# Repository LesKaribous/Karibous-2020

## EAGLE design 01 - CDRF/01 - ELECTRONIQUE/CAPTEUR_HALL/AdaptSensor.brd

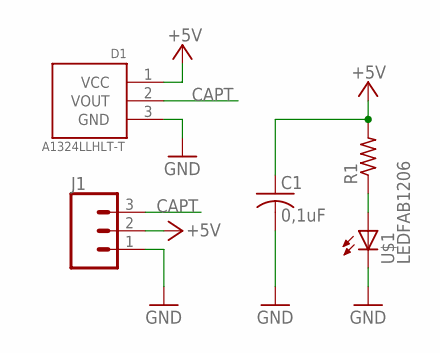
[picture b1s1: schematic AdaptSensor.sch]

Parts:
C1: 0,1uF; C1206FAB
D1: A1324LLHLT-T; SOT190P290X100-3N
J1: CONN_03POLAR; MOLEX-1X3
R1: RES-US1206FAB; R1206FAB
U$1: LEDFAB1206; LED1206FAB

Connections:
+5V: C1.1, D1.1 (VCC), J1.2, R1.2
CAPT: D1.2 (VOUT), J1.3
GND: C1.2, D1.3 (GND), J1.1, U$1.2 (C)
unnamed: R1.1, U$1.1 (A)

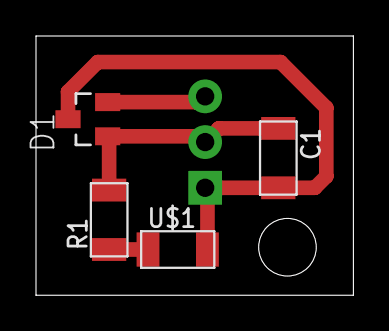
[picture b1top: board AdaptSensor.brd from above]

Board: 2 copper layers, 17.6 x 14.4 mm, 5 parts (1 on the bottom side), 4 nets.

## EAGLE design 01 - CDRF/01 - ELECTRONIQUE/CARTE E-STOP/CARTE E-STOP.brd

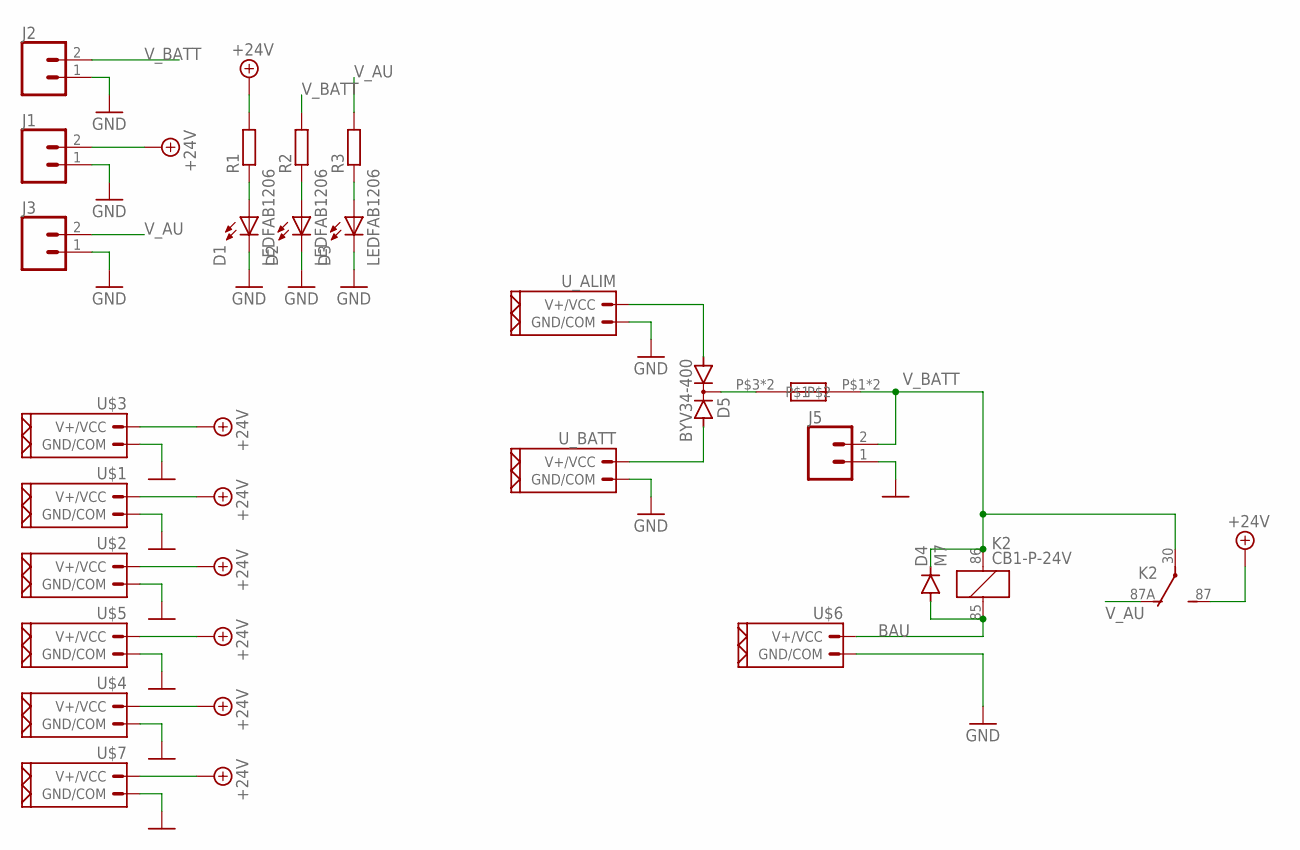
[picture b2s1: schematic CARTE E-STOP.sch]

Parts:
D1, D2, D3: LEDFAB1206; LED1206FAB
D4: M7; SMA-DO214AC
D5: BYV34-400; TO220ABS
J1, J2, J3, J5: CONN_02POLAR; MOLEX-1X2
K2: CB1-P-24V; CB1
R1, R2, R3: R-EU_M1206; M1206
U$1, U$2, U$3, U$4, U$5, U$7: CONN_02_PUIXT30; XT30_FEMALE
U$6: CONN_02_PUI; NSK396-2C
U$8: AUTOMOTIVE_FUSE3557-2; 3557-2
U_ALIM: CONN_02_PUIXT60; XT60
U_BATT: CONN_02_PUIXT60; XT60

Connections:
+24V: J1.2, K2.87 (S), R1.2, U$1.P$1 (V+/VCC), U$2.P$1 (V+/VCC), U$3.P$1 (V+/VCC), U$4.P$1 (V+/VCC), U$5.P$1 (V+/VCC), U$7.P$1 (V+/VCC)
BAU: D4.A, K2.85 (2), U$6.P$2 (V+/VCC)
GND: D1.2 (C), D2.2 (C), D3.2 (C), J1.1, J2.1, J3.1, J5.1, U$1.P$2 (GND/COM), U$2.P$2 (GND/COM), U$3.P$2 (GND/COM), U$4.P$2 (GND/COM), U$5.P$2 (GND/COM), U$6.P$1 (GND/COM), U$7.P$2 (GND/COM), U_ALIM.P$2 (GND/COM), U_BATT.P$2 (GND/COM)
unnamed: D1.1 (A), R1.1
unnamed: D2.1 (A), R2.1
unnamed: D3.1 (A), R3.1
unnamed: D5.A1, U_ALIM.P$1 (V+/VCC)
unnamed: D5.C, U$8.P$3, U$8.P$4
unnamed: D5.A2, U_BATT.P$1 (V+/VCC)
V_AU: J3.2, K2.87A (O), R3.2
V_BATT: D4.K (C), J2.2, J5.2, K2.30, K2.86 (1), R2.2, U$8.P$1, U$8.P$2

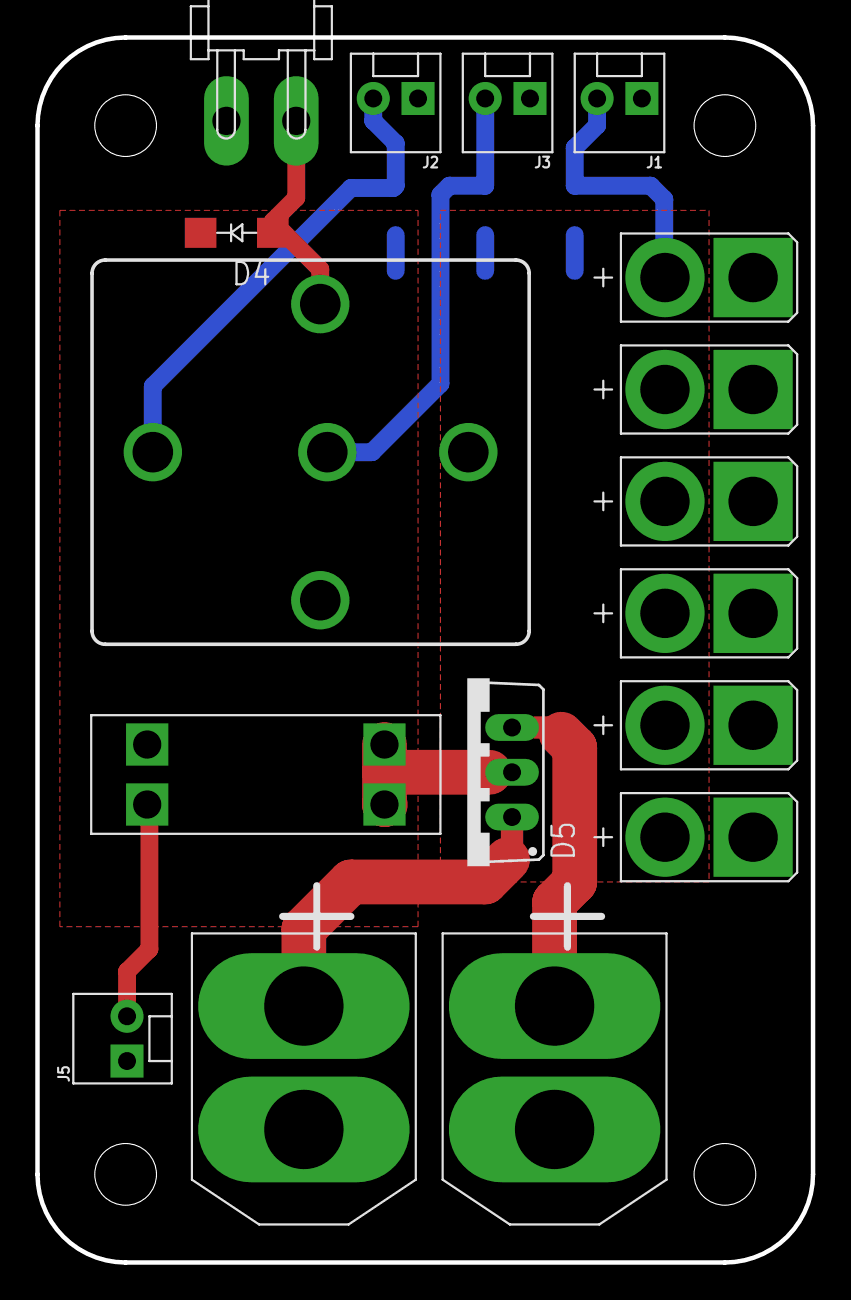
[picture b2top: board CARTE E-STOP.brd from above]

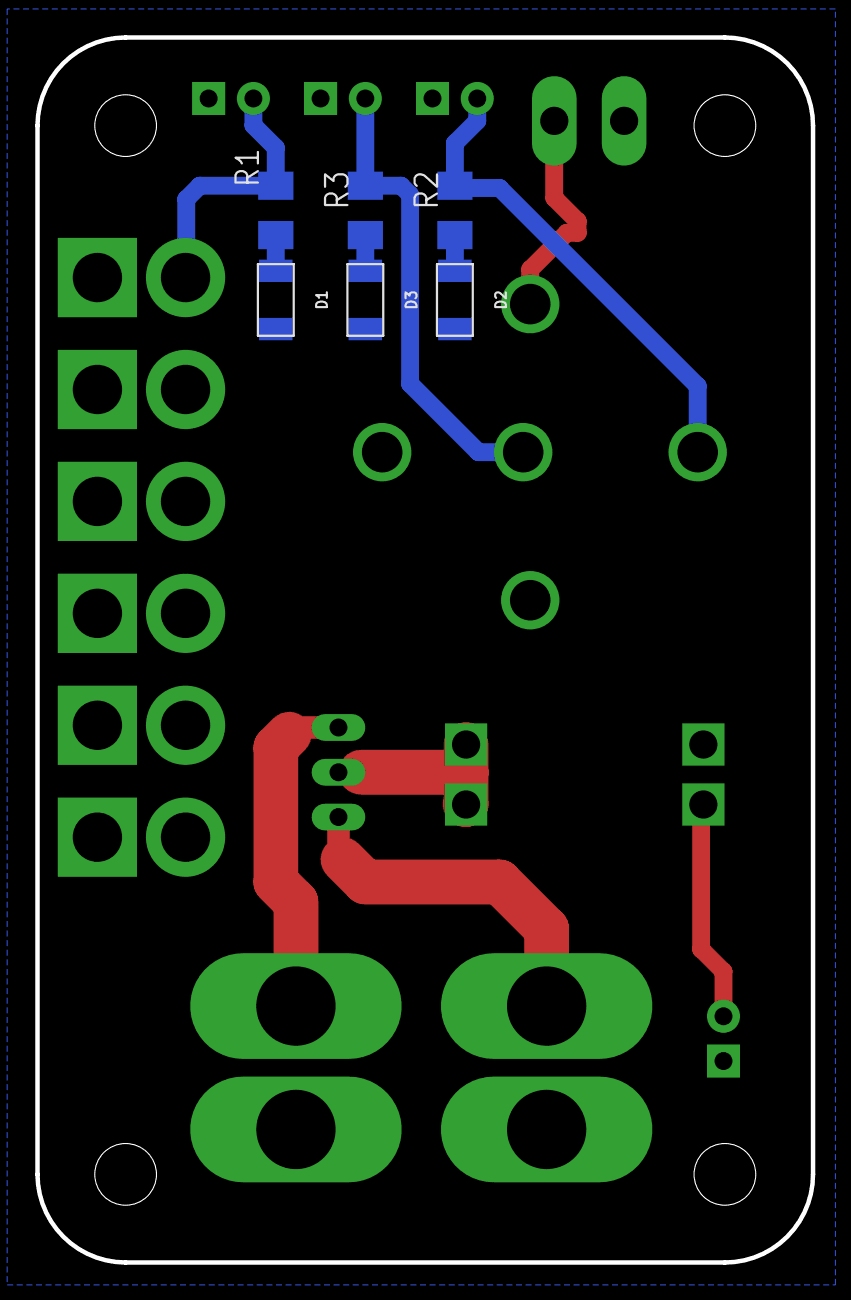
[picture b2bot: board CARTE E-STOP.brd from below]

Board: 2 copper layers, 44.0 x 69.5 mm, 23 parts (6 on the bottom side), 11 nets.

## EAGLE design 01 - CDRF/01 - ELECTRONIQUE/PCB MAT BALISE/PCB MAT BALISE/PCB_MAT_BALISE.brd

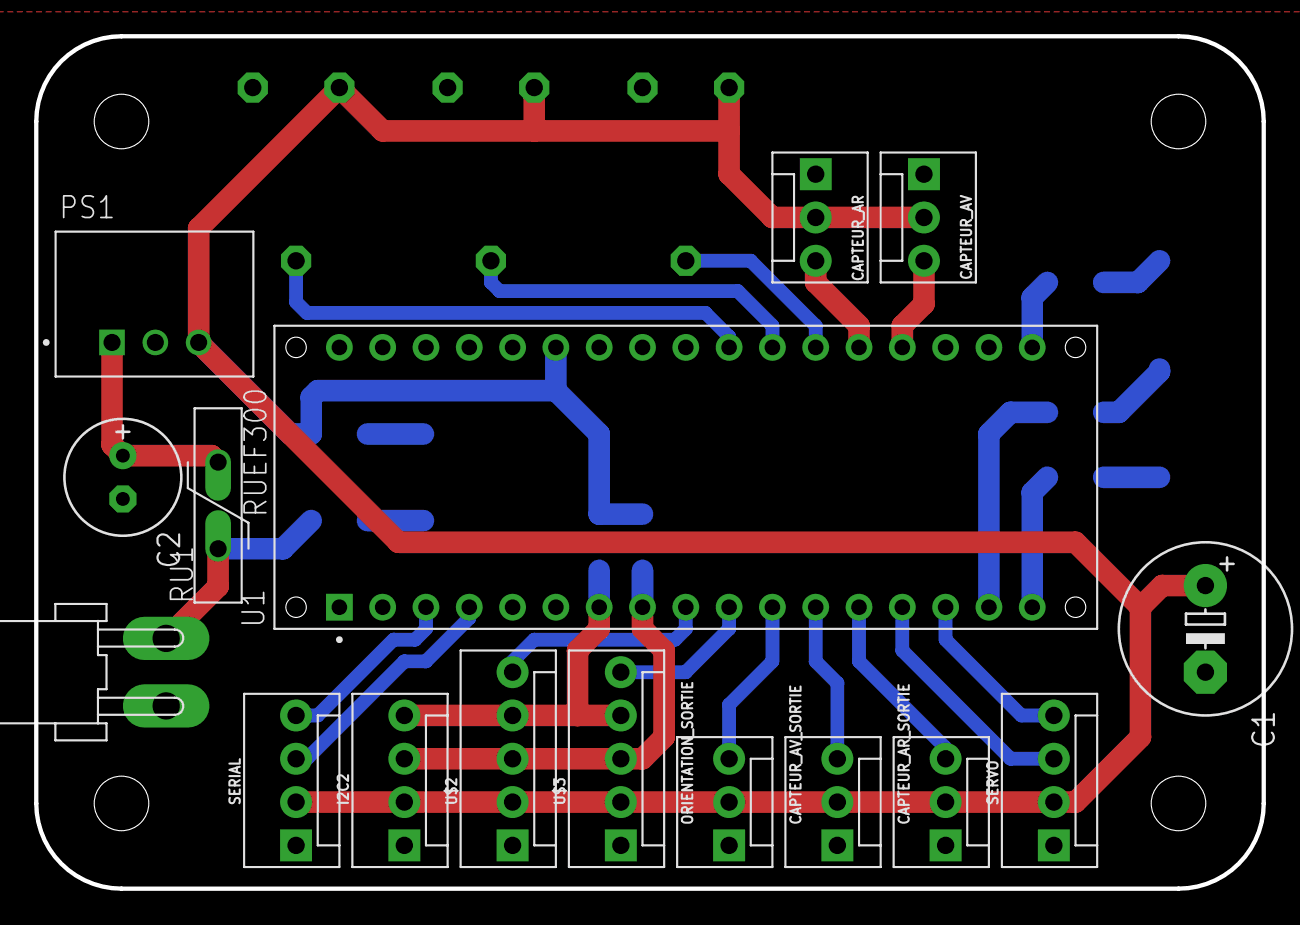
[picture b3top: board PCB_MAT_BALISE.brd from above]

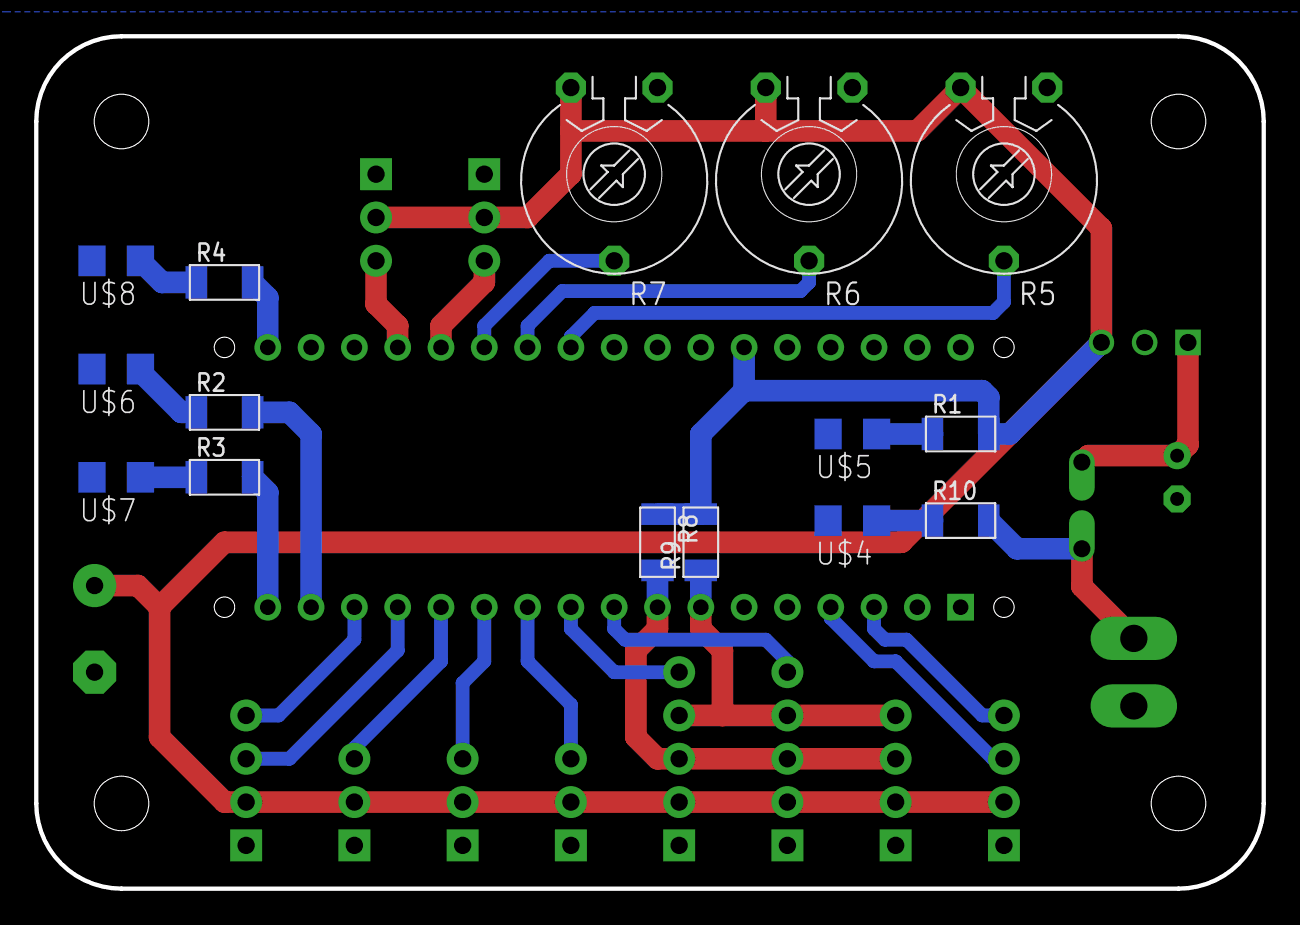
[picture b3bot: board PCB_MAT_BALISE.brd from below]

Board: 2 copper layers, 72.0 x 50.0 mm, 31 parts (15 on the bottom side), 28 nets.

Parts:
C1: 470uF; E5-10,5
C2: 10uF; E2,5-7
CAPTEUR_AR: MOLEX-1X3
CAPTEUR_AR_SORTIE: MOLEX-1X3
CAPTEUR_AV: MOLEX-1X3
CAPTEUR_AV_SORTIE: MOLEX-1X3
I2C2: MOLEX-1X4
ORIENTATION_SORTIE: MOLEX-1X3
PS1: R-78E5.0-1.0; CONV_R-78E5.0-1.0
R1, R2, R3, R4, R8, R9, R10: R1206FAB
R5, R6, R7: PT-10
RU1: RUEF300
SERIAL: MOLEX-1X4
SERVO: MOLEX-1X4
U1: A000053; ARDUINO_A000053
U$1: CONN_02_PUI; NSK396-2C
U$2, U$3: CONN_05; MOLEX-1X5
U$4, U$5, U$6, U$7, U$8: LED; LED1206

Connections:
+5V: C1.+, CAPTEUR_AR.2, CAPTEUR_AR_SORTIE.2, CAPTEUR_AV.2, CAPTEUR_AV_SORTIE.2, I2C2.2, ORIENTATION_SORTIE.2, PS1.3, R1.2, R5.2, R6.2, R7.2, R8.1, R9.2, SERIAL.2, SERVO.2, U1.29, U$2.2, U$3.2
+24V: R10.2, RU1.P$1, U$1.P$2
CAPT_AR: CAPTEUR_AR.3, U1.22
CAPT_AR_SORTIE: CAPTEUR_AR_SORTIE.3, U1.13
CAPT_AV: CAPTEUR_AV.3, U1.21
CAPT_AV_SORTIE: CAPTEUR_AV_SORTIE.3, U1.12
DETECT_AR: R3.2, U1.17
DETECT_AV: R2.2, U1.16
EMITT_1: R4.2, U1.18
GND: C1.-, C2.-, CAPTEUR_AR.1, CAPTEUR_AR_SORTIE.1, CAPTEUR_AV.1, CAPTEUR_AV_SORTIE.1, I2C2.1, ORIENTATION_SORTIE.1, PS1.2, R5.1, R6.1, R7.1, SERIAL.1, SERVO.1, U1.6, U1.31, U$1.P$1, U$2.1, U$3.1, U$4.2, U$5.2, U$6.2, U$7.2, U$8.2
unnamed: R1.1, U$5.1
unnamed: R2.1, U$6.1
unnamed: R3.1, U$7.1
unnamed: R4.1, U$8.1
unnamed: C2.+, PS1.1, RU1.P$2
unnamed: R10.1, U$4.1
ORIENTATION_SORTIE: ORIENTATION_SORTIE.3, U1.11
RX: SERIAL.3, U1.4
SCL: I2C2.3, R8.2, U1.8, U$2.3, U$3.3
SDA: I2C2.4, R9.1, U1.7, U$2.4, U$3.4
SIGNAL_1: R6.3, U1.24
SIGNAL_2: R5.3, U1.25
SIGNAL_ORIENTATION: SERVO.3, U1.14
SIGNAL_SERVO: SERVO.4, U1.15
TX: SERIAL.4, U1.3
VITESSE_SERVO: R7.3, U1.23
XSHUT_AR: U1.9, U$2.5
XSHUT_AV: U1.10, U$3.5

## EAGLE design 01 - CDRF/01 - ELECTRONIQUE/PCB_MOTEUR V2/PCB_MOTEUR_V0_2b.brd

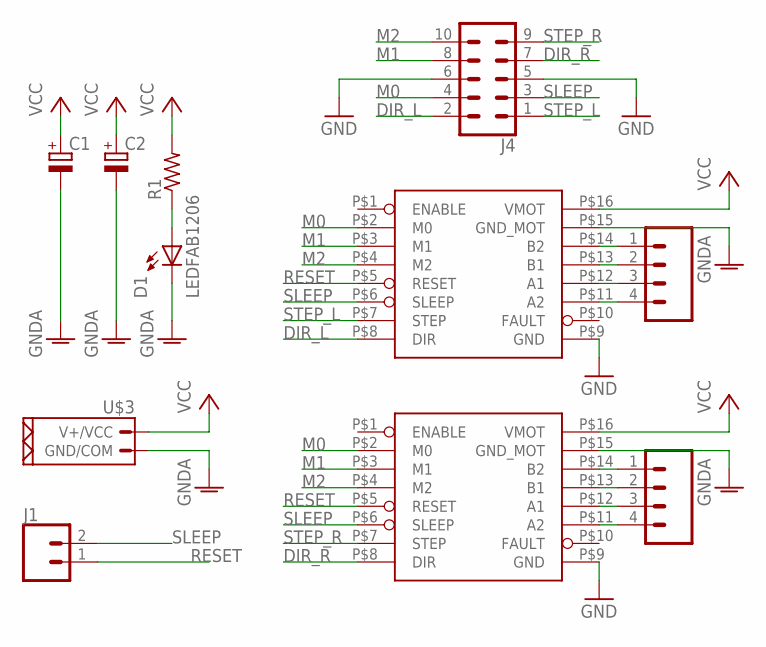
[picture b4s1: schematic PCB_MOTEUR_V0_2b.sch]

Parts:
C1, C2: CPOL-EUE3.5-8; E3,5-8
D1: LEDFAB1206; LED1206FAB
J1: CONN_02; 1X02
J3, J5: CONN_04POLAR; MOLEX-1X4
J4: CONN_05X2SHD; 2X5-SHROUDED
R1: RES-US1206FAB; R1206FAB
U$1, U$2: DRV8825; DRIVER_CARRIER_POLOLU_16
U$3: CONN_02_PUIXT30; XT30_FEMALE

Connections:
DIR_L: J4.2, U$1.P$8 (DIR)
DIR_R: J4.7, U$2.P$8 (DIR)
GND: J4.5, J4.6, U$1.P$9 (GND), U$2.P$9 (GND)
GNDA: C1.-, C2.-, D1.2 (C), U$1.P$15 (GND_MOT), U$2.P$15 (GND_MOT), U$3.P$2 (GND/COM)
M0: J4.4, U$1.P$2 (M0), U$2.P$2 (M0)
M1: J4.8, U$1.P$3 (M1), U$2.P$3 (M1)
M2: J4.10, U$1.P$4 (M2), U$2.P$4 (M2)
unnamed: J3.1, U$1.P$14 (B2)
unnamed: J3.2, U$1.P$13 (B1)
unnamed: J3.3, U$1.P$12 (A1)
unnamed: J3.4, U$1.P$11 (A2)
unnamed: D1.1 (A), R1.1
unnamed: J5.1, U$2.P$14 (B2)
unnamed: J5.2, U$2.P$13 (B1)
unnamed: J5.3, U$2.P$12 (A1)
unnamed: J5.4, U$2.P$11 (A2)
RESET: J1.1, U$1.P$5 (RESET), U$2.P$5 (RESET)
SLEEP: J1.2, J4.3, U$1.P$6 (SLEEP), U$2.P$6 (SLEEP)
STEP_L: J4.1, U$1.P$7 (STEP)
STEP_R: J4.9, U$2.P$7 (STEP)
VCC: C1.+, C2.+, R1.2, U$1.P$16 (VMOT), U$2.P$16 (VMOT), U$3.P$1 (V+/VCC)

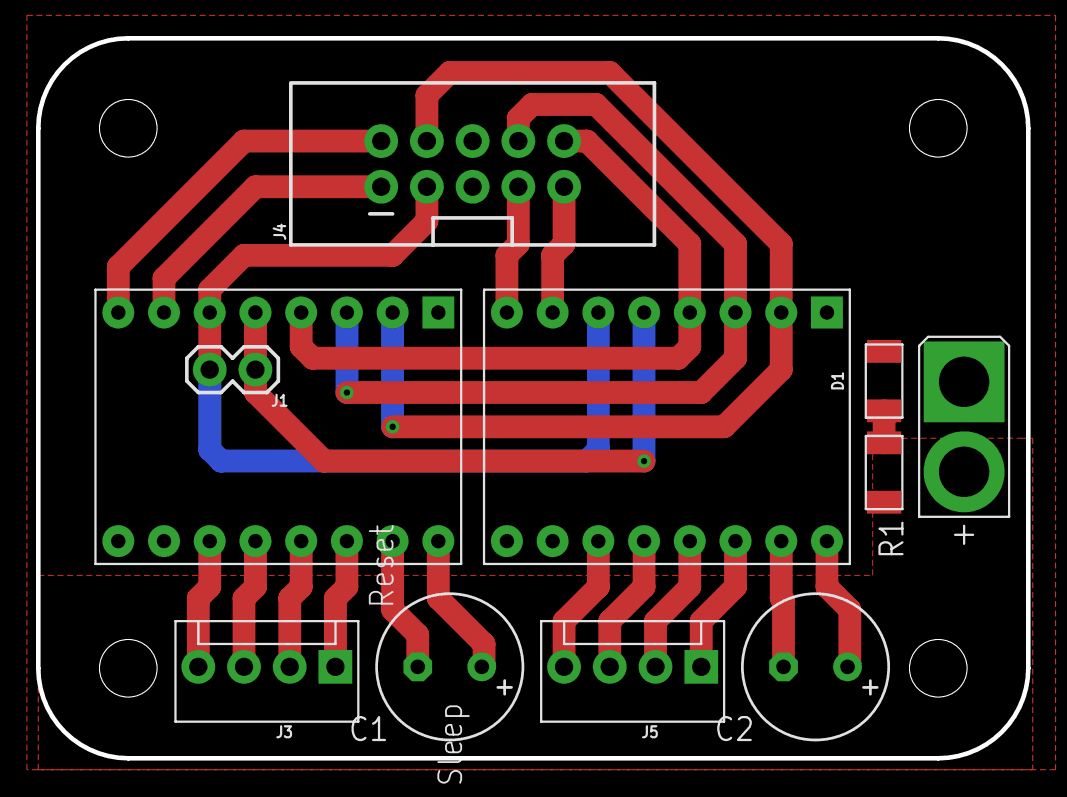
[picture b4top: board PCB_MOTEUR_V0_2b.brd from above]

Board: 2 copper layers, 55.0 x 40.0 mm, 11 parts (0 on the bottom side), 21 nets.

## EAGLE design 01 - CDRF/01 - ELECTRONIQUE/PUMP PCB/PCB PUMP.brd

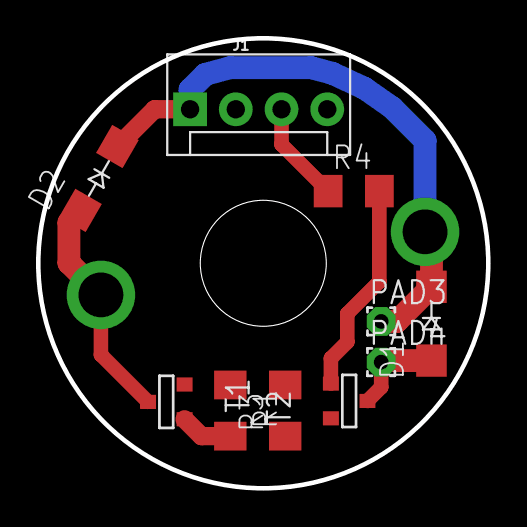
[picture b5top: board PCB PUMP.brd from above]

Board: 2 copper layers, 25.0 x 25.0 mm, 13 parts (1 on the bottom side), 8 nets.

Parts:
D1, D2: GF1; SMA-DO214AC
J1: MOLEX-1X4
J3, J4: PWRPAD2-5MM; PWRPAD_2-5MM
PAD3, PAD4: WIREPAD1,6/0,8; 1,6/0,8
R1, R3: 10k; R1206
R2, R4: 1K; R1206
T1, T2: SOT-23

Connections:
+5V: D1.K, D2.K, J1.1, J4.P$1, PAD3.1
EV: J1.3, R4.1
GND: J1.4, R1.1, R3.1, T1.2, T2.2
unnamed: D1.A, PAD4.1, T2.1
unnamed: D2.A, J3.P$1, T1.1
unnamed: R1.2, R2.2, T1.3
unnamed: R3.2, R4.2, T2.3
PUMP: J1.2, R2.1

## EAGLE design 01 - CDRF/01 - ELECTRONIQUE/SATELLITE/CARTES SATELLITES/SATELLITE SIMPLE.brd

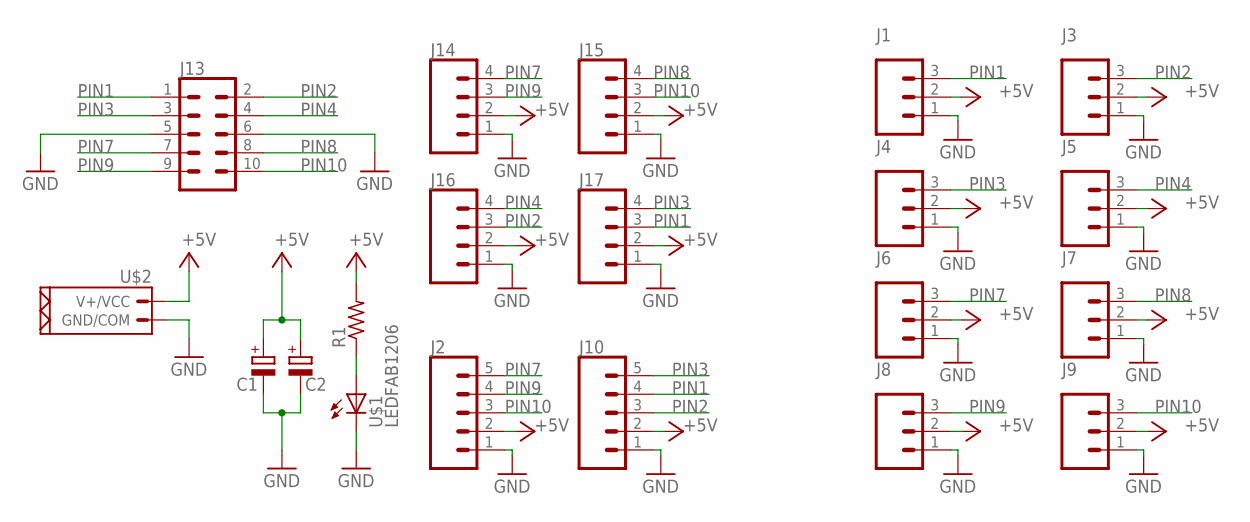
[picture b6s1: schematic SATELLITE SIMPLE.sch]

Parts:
C1, C2: CPOL-EUE5-10.5; E5-10,5
J1, J3, J4, J5, J6, J7, J8, J9: CONN_03POLAR; MOLEX-1X3
J2, J10: CONN_05; MOLEX-1X5
J13: CONN_05X2SHD; 2X5-SHROUDED
J14, J15, J16, J17: CONN_04POLAR; MOLEX-1X4
R1: RES-US1206FAB; R1206FAB
U$1: LEDFAB1206; LED1206FAB
U$2: CONN_02_PUI; NSK396-2C

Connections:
+5V: C1.+, C2.+, J1.2, J2.2, J3.2, J4.2, J5.2, J6.2, J7.2, J8.2, J9.2, J10.2, J14.2, J15.2, J16.2, J17.2, R1.2, U$2.P$2 (V+/VCC)
GND: C1.-, C2.-, J1.1, J2.1, J3.1, J4.1, J5.1, J6.1, J7.1, J8.1, J9.1, J10.1, J13.5, J13.6, J14.1, J15.1, J16.1, J17.1, U$1.2 (C), U$2.P$1 (GND/COM)
unnamed: R1.1, U$1.1 (A)
PIN1: J1.3, J10.4, J13.1, J17.3
PIN2: J3.3, J10.3, J13.2, J16.3
PIN3: J4.3, J10.5, J13.3, J17.4
PIN4: J5.3, J13.4, J16.4
PIN7: J2.5, J6.3, J13.7, J14.4
PIN8: J7.3, J13.8, J15.4
PIN9: J2.4, J8.3, J13.9, J14.3
PIN10: J2.3, J9.3, J13.10, J15.3

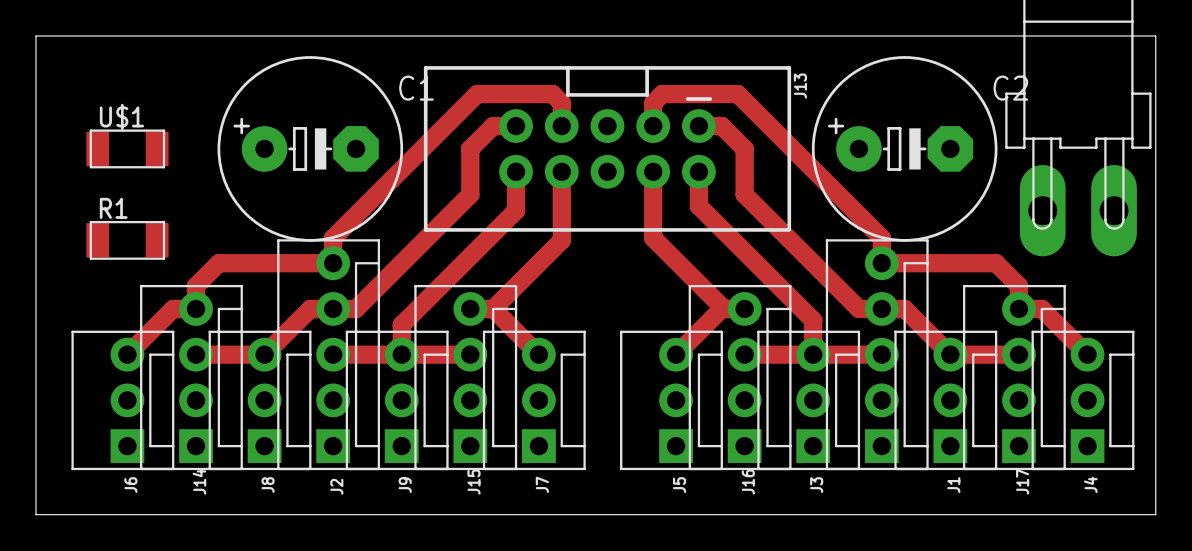
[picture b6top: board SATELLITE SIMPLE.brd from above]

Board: 2 copper layers, 62.2 x 26.6 mm, 20 parts (0 on the bottom side), 11 nets.
